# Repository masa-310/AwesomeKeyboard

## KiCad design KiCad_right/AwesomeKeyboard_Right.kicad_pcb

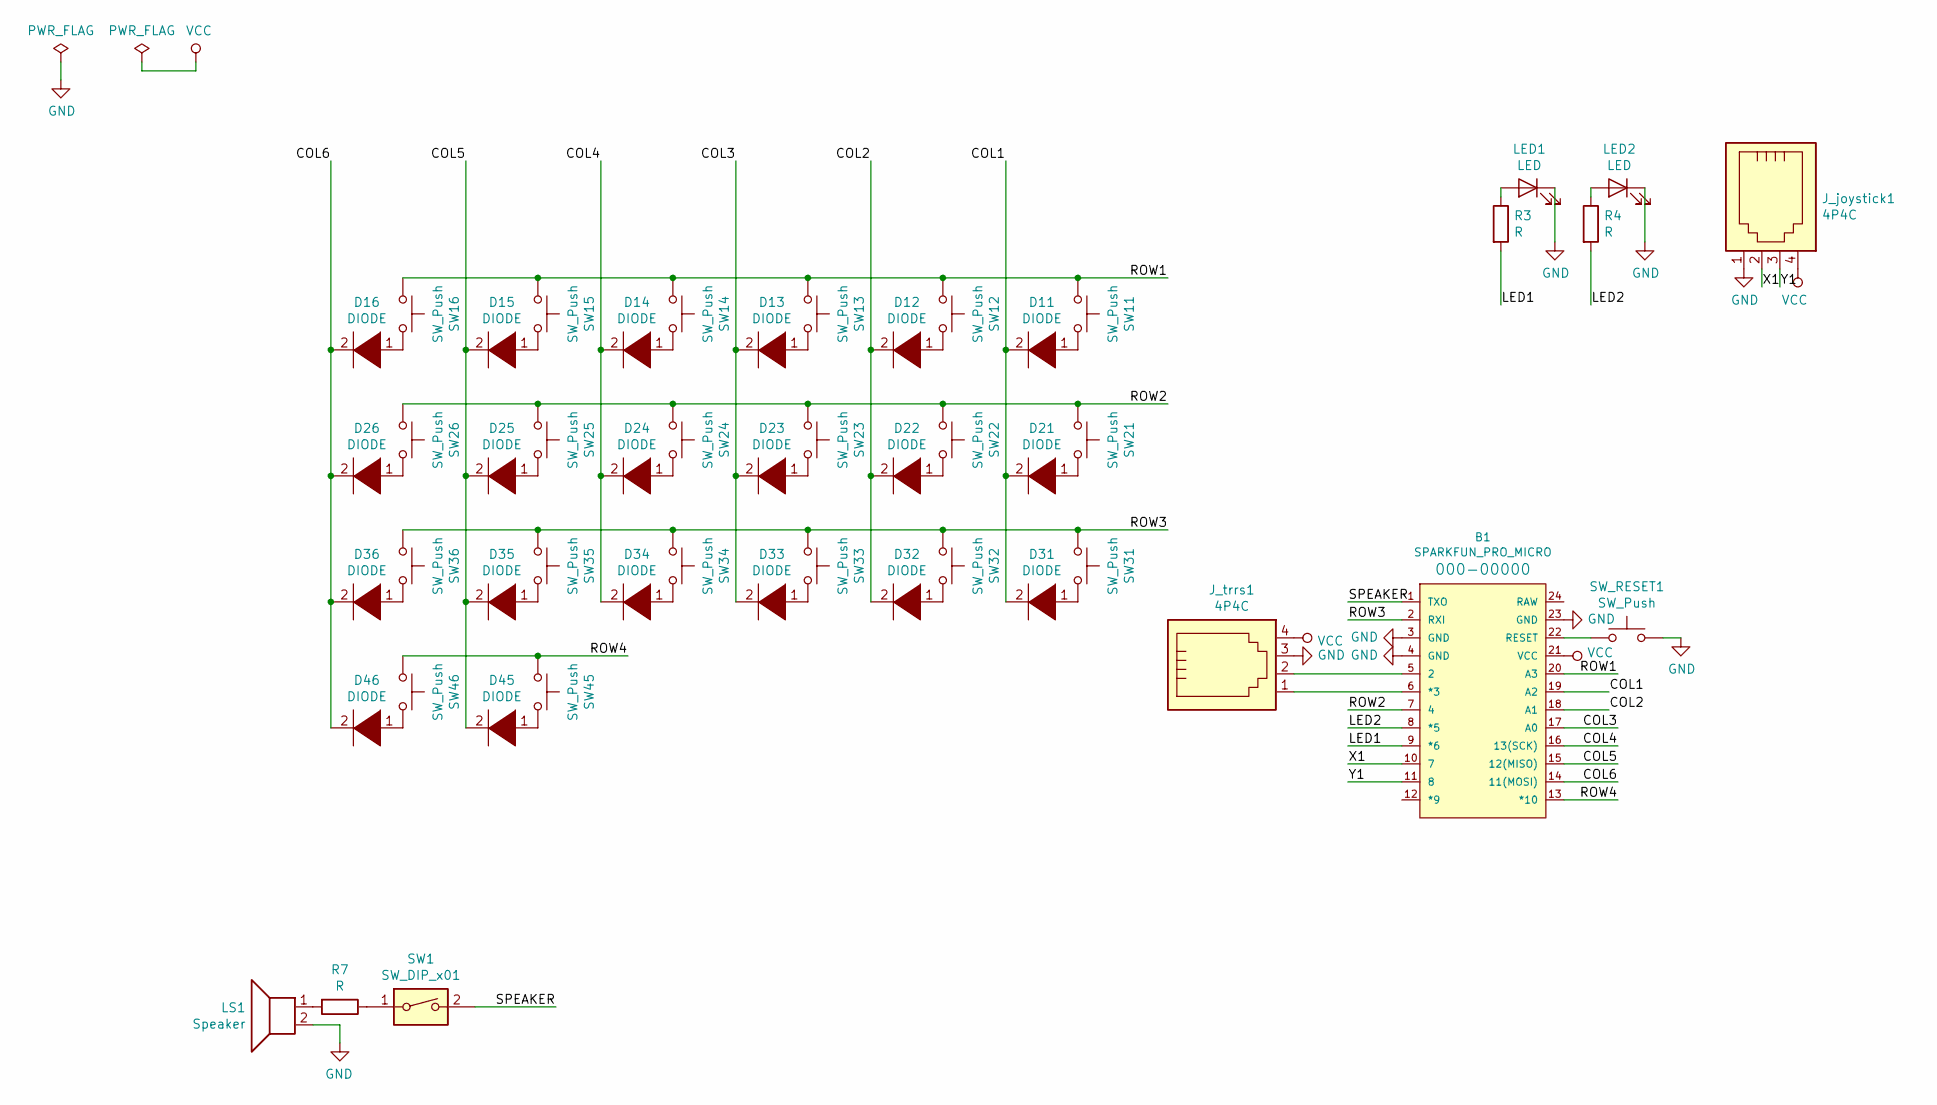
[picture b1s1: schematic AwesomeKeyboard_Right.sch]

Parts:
B1: SPARKFUN_PRO_MICRO
D11, D12, D13, D14, D15, D16, D21, D22, D23, D24, D25, D26, D31, D32, D33, D34, D35, D36, D45, D46: DIODE; D_DO-35_SOD27_P7.62mm_Horizontal
J_joystick1: 4P4C; PinHeader_1x04_P2.00mm_Vertical
J_trrs1: 4P4C; PinHeader_1x04_P2.00mm_Vertical
LED1, LED2: LED; LED_D5.0mm
LS1: Speaker; Buzzer_12x9.5RM7.6
R3, R4, R7: R; R_Axial_DIN0204_L3.6mm_D1.6mm_P7.62mm_Horizontal
SW1: SW_DIP_x01; SW_DIP_SPSTx01_Slide_6.7x4.1mm_W7.62mm_P2.54mm_LowProfile
SW11, SW12, SW13, SW14, SW15, SW16, SW21, SW22, SW23, SW24, SW25, SW26, SW31, SW32, SW33, SW34, SW35, SW36, SW45, SW46: SW_Push; SW_Cherry_MX1A_1.00u_Plate
SW_RESET1: SW_Push; SW_PUSH_6mm

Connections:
/COL1: B1.19 (A2), D11.2 (A), D21.2 (A), D31.2 (A)
/COL2: B1.18 (A1), D12.2 (A), D22.2 (A), D32.2 (A)
/COL3: B1.17 (A0), D13.2 (A), D23.2 (A), D33.2 (A)
/COL4: B1.16 (13(SCK)), D14.2 (A), D24.2 (A), D34.2 (A)
/COL5: B1.15 (12(MISO)), D15.2 (A), D25.2 (A), D35.2 (A), D45.2 (A)
/COL6: B1.14 (11(MOSI)), D16.2 (A), D26.2 (A), D36.2 (A), D46.2 (A)
/LED1: B1.9 (*6), R3.2
/LED2: B1.8 (*5), R4.2
/ROW1: B1.20 (A3), SW11.1, SW12.1, SW13.1, SW14.1, SW15.1, SW16.1
/ROW2: B1.7 (4), SW21.1, SW22.1, SW23.1, SW24.1, SW25.1, SW26.1
/ROW3: B1.2 (RXI), SW31.1, SW32.1, SW33.1, SW34.1, SW35.1, SW36.1
/ROW4: B1.13 (*10), SW45.1, SW46.1
/SPEAKER: B1.1 (TXO), SW1.2
/X1: B1.10 (7), J_joystick1.2
/Y1: B1.11 (8), J_joystick1.3
GND: B1.3 (GND), B1.4 (GND), B1.23 (GND), J_joystick1.1, J_trrs1.3, LED1.1 (K), LED2.1 (K), LS1.2, SW_RESET1.2
unnamed: B1.5 (2), J_trrs1.2
unnamed: B1.6 (*3), J_trrs1.1
unnamed: B1.22 (RESET), SW_RESET1.1
unnamed: D11.1 (K), SW11.2
unnamed: D12.1 (K), SW12.2
unnamed: D13.1 (K), SW13.2
unnamed: D14.1 (K), SW14.2
unnamed: D15.1 (K), SW15.2
unnamed: D16.1 (K), SW16.2
unnamed: D21.1 (K), SW21.2
unnamed: D22.1 (K), SW22.2
unnamed: D23.1 (K), SW23.2
unnamed: D24.1 (K), SW24.2
unnamed: D25.1 (K), SW25.2
unnamed: D26.1 (K), SW26.2
unnamed: D31.1 (K), SW31.2
unnamed: D32.1 (K), SW32.2
unnamed: D33.1 (K), SW33.2
unnamed: D34.1 (K), SW34.2
unnamed: D35.1 (K), SW35.2
unnamed: D36.1 (K), SW36.2
unnamed: D45.1 (K), SW45.2
unnamed: D46.1 (K), SW46.2
unnamed: LED1.2 (A), R3.1
unnamed: LED2.2 (A), R4.1
unnamed: LS1.1, R7.2
unnamed: R7.1, SW1.1
VCC: B1.21 (VCC), J_joystick1.4, J_trrs1.4

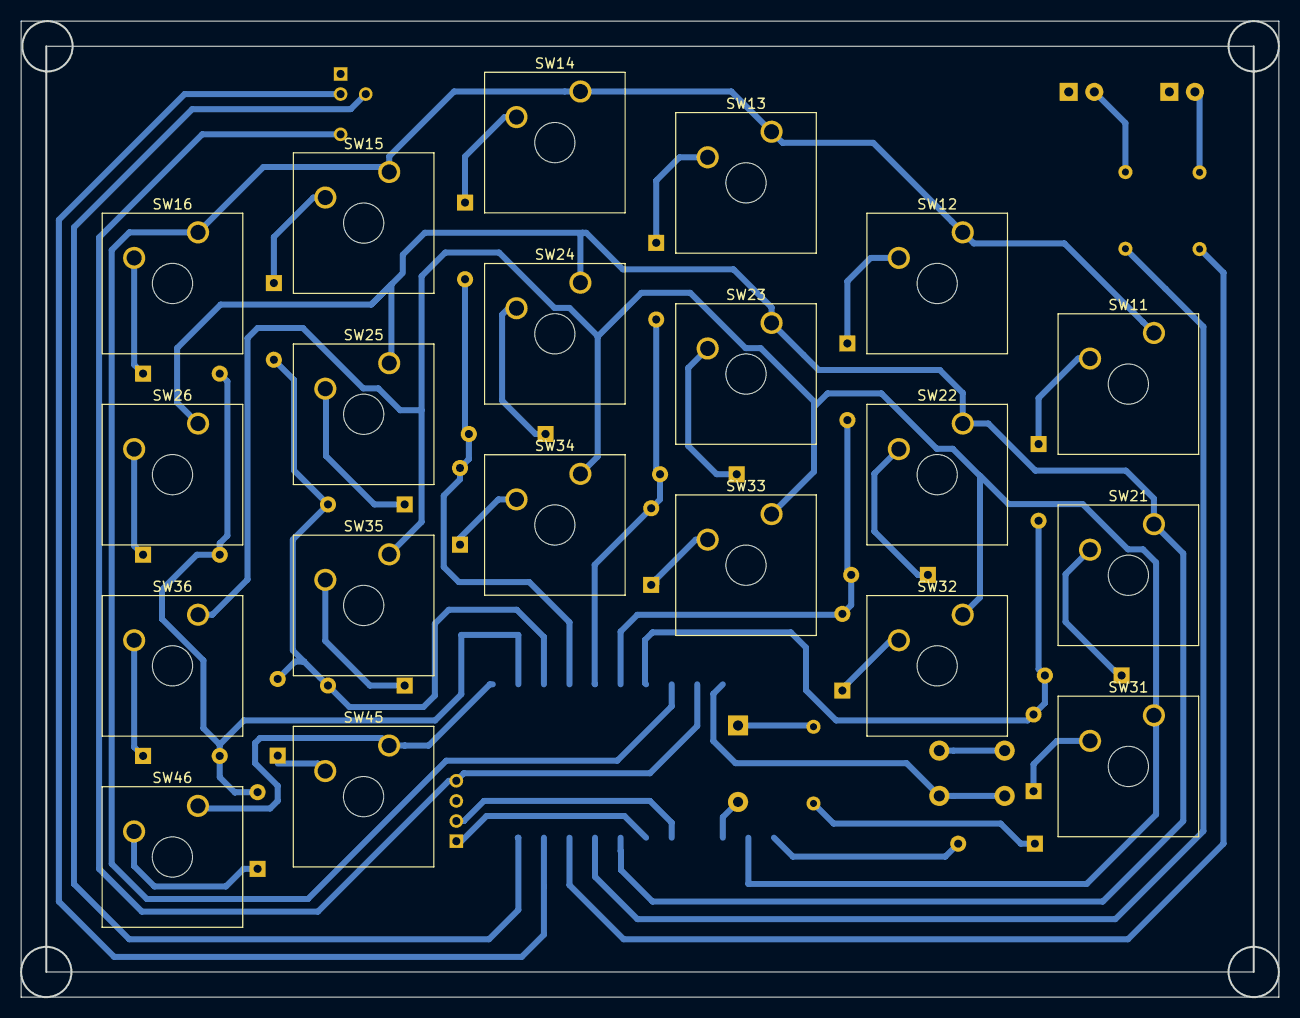
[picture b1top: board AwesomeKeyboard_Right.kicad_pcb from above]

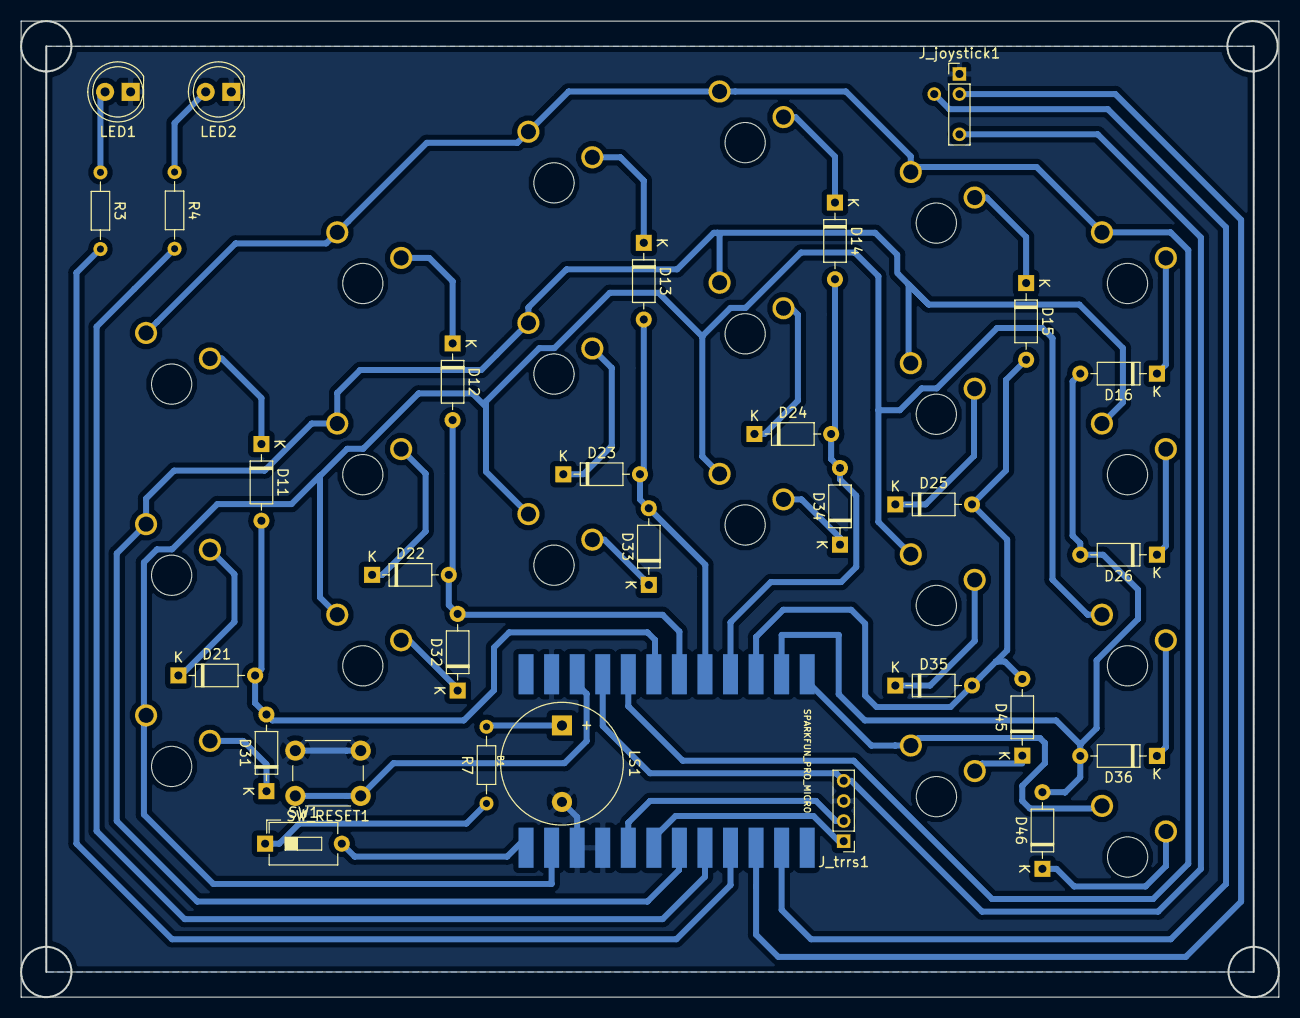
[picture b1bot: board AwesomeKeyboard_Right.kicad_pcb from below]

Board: 2 copper layers, 125.0 x 97.0 mm, 51 parts (31 on the bottom side), 44 nets.

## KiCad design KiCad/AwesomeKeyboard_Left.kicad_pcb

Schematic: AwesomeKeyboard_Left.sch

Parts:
B1: SPARKFUN_PRO_MICRO
C1: C; CP_Elec_3x5.3
D11, D12, D13, D14, D15, D16, D21, D22, D23, D24, D25, D26, D31, D32, D33, D34, D35, D36, D45, D46: DIODE; D_SOD-123
J1: AudioJack4_Ground; Jack_3.5mm_PJ320D_Horizontal
LED1, LED2, LED3, LED4: LED; LED_D5.0mm
LS1: Speaker; Buzzer_Murata_PKMCS0909E4000-R1
R1, R2, R3, R4, R5, R6, R7: R; R_Axial_DIN0204_L3.6mm_D1.6mm_P7.62mm_Horizontal
SW1: SW_DIP_x01; SW_DIP_SPSTx01_Slide_6.7x4.1mm_W6.73mm_P2.54mm_LowProfile_J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
SW11, SW12, SW13, SW14, SW15, SW16, SW21, SW22, SW23, SW24, SW25, SW26, SW31, SW32, SW33, SW34, SW35, SW36, SW45, SW46: SW_Push; SW_Cherry_MX1A_1.00u_Plate
SW_RESET1: SW_Push; SW_SPST_FSMSM

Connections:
/COL1: B1.1 (TXO), D11.2 (A), D21.2 (A), D31.2 (A)
/COL2: B1.2 (RXI), D12.2 (A), D22.2 (A), D32.2 (A)
/COL3: B1.8 (*5), D13.2 (A), D23.2 (A), D33.2 (A)
/COL4: B1.9 (*6), D14.2 (A), D24.2 (A), D34.2 (A)
/COL5: B1.10 (7), D15.2 (A), D25.2 (A), D35.2 (A), D45.2 (A)
/COL6: B1.11 (8), D16.2 (A), D26.2 (A), D36.2 (A), D46.2 (A)
/LED1: B1.13 (*10), R3.2
/LED2: B1.14 (11(MOSI)), R4.2
/LED3: B1.15 (12(MISO)), R5.2
/LED4: B1.16 (13(SCK)), R6.2
/ROW1: B1.17 (A0), SW11.2, SW12.2, SW13.2, SW14.2, SW15.2, SW16.2
/ROW2: B1.18 (A1), SW21.2, SW22.2, SW23.2, SW24.2, SW25.2, SW26.2
/ROW3: B1.19 (A2), SW31.2, SW32.2, SW33.2, SW34.2, SW35.2, SW36.2
/ROW4: B1.12 (*9), SW45.2, SW46.2
/SPEAKER: B1.20 (A3), SW1.2
GND: B1.3 (GND), B1.23 (GND), C1.2, J1.4, LED1.1 (K), LED2.1 (K), LED3.1 (K), LED4.1 (K), LS1.2, SW_RESET1.2
unnamed: B1.5 (2), J1.2, R2.2
unnamed: B1.6 (*3), J1.1, R1.2
unnamed: B1.22 (RESET), SW_RESET1.1
unnamed: D11.1 (K), SW11.1
unnamed: D12.1 (K), SW12.1
unnamed: D13.1 (K), SW13.1
unnamed: D14.1 (K), SW14.1
unnamed: D15.1 (K), SW15.1
unnamed: D16.1 (K), SW16.1
unnamed: D21.1 (K), SW21.1
unnamed: D22.1 (K), SW22.1
unnamed: D23.1 (K), SW23.1
unnamed: D24.1 (K), SW24.1
unnamed: D25.1 (K), SW25.1
unnamed: D26.1 (K), SW26.1
unnamed: D31.1 (K), SW31.1
unnamed: D32.1 (K), SW32.1
unnamed: D33.1 (K), SW33.1
unnamed: D34.1 (K), SW34.1
unnamed: D35.1 (K), SW35.1
unnamed: D36.1 (K), SW36.1
unnamed: D45.1 (K), SW45.1
unnamed: D46.1 (K), SW46.1
unnamed: LED1.2 (A), R3.1
unnamed: LED2.2 (A), R4.1
unnamed: LED3.2 (A), R5.1
unnamed: LED4.2 (A), R6.1
unnamed: LS1.1, R7.2
unnamed: R7.1, SW1.1
VCC: B1.21 (VCC), C1.1, J1.3, R1.1, R2.1

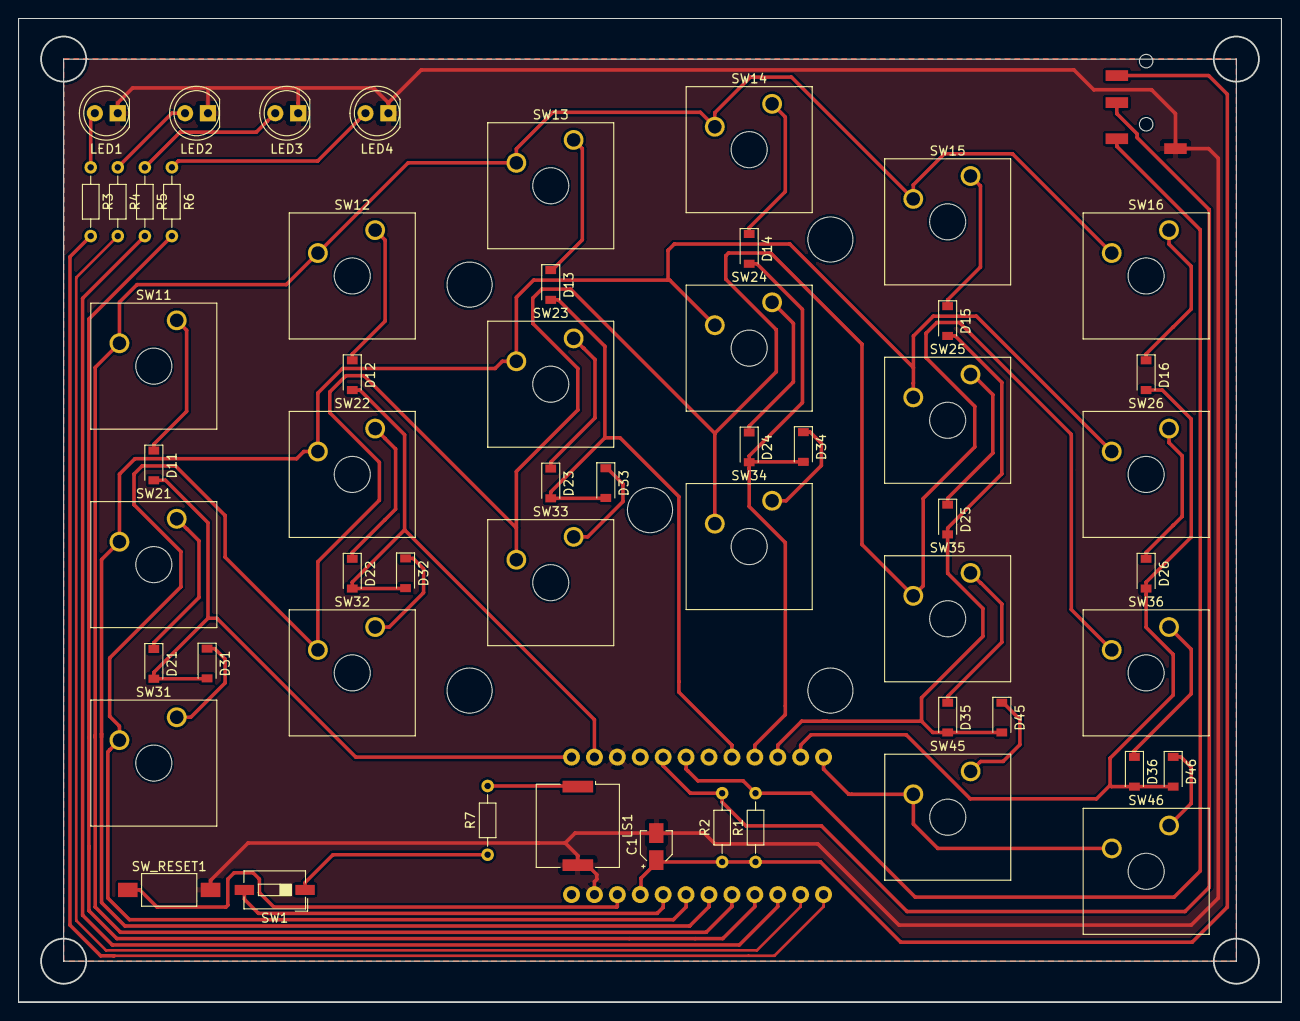
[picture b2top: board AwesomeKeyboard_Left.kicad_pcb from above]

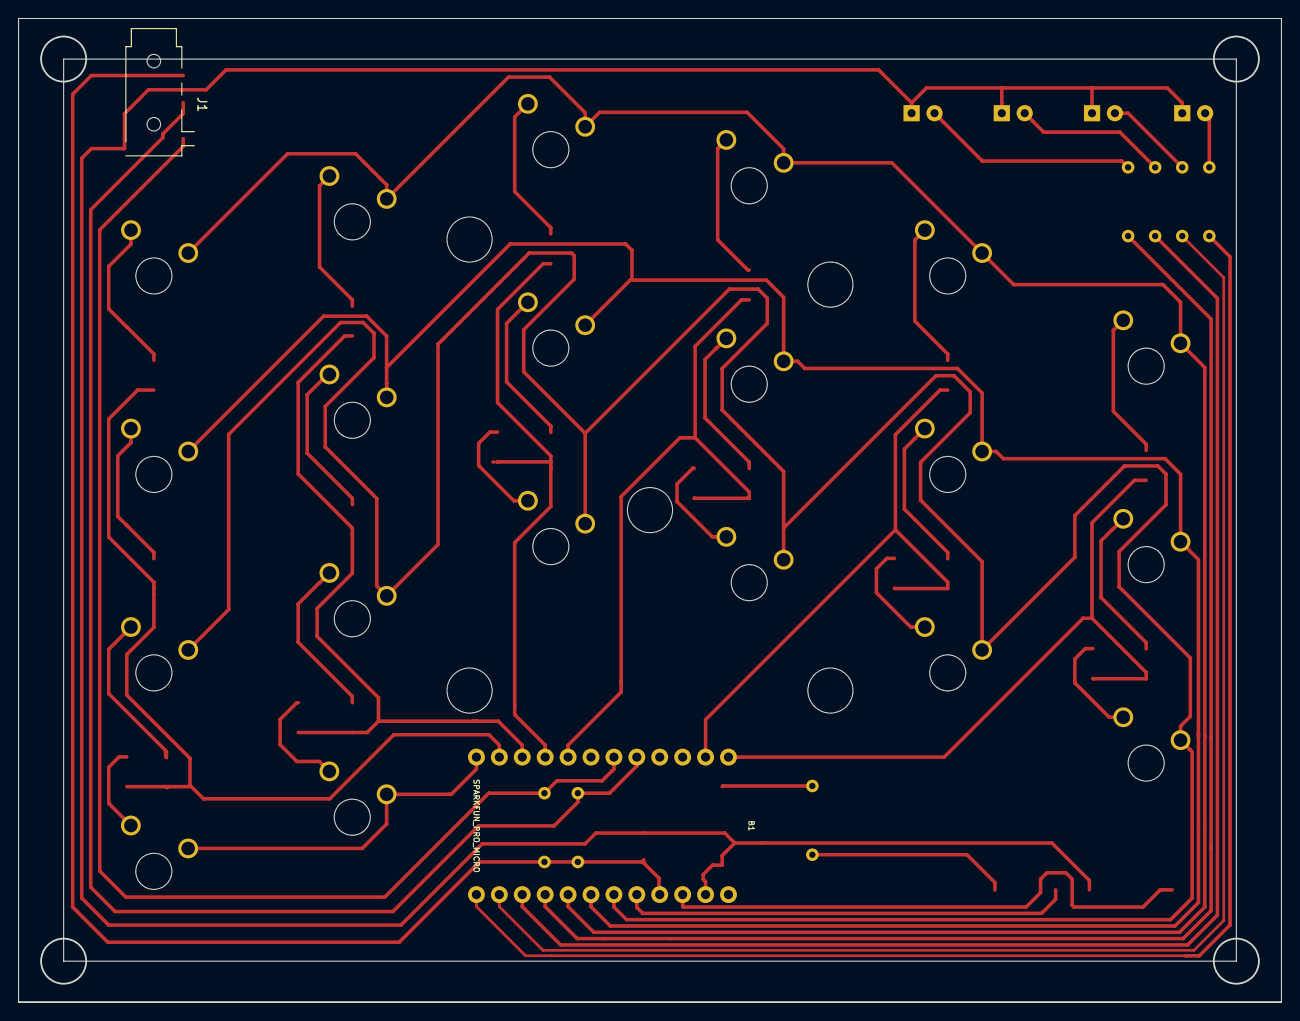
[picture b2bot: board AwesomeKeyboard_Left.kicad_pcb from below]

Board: 2 copper layers, 140.0 x 109.0 mm, 57 parts (2 on the bottom side), 46 nets.

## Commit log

2018-12-04 folder
2018-12-05 add bypass condenser
2018-12-05 fix something
2018-12-06 modify
2018-12-16 left
2018-12-16 add right keyboard
2018-12-16 rename left to right
2018-12-28 right
2018-12-29 restart
